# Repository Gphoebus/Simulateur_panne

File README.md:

<div align="center">

# 🔧 Simulateur de pannes BLE

**Carte d'interposition 4 voies pilotée par smartphone pour provoquer des pannes réalistes sur un système automatisé didactique, sans toucher au câblage.**

[Principe](#-principe) •
[Démarrage rapide](#-démarrage-rapide) •
[Matériel](#-matériel) •
[Firmware](#-firmware-esp32-c3) •
[Application](#-application-android-simu-pannes) •
[Protocole BLE](#-protocole-ble) •
[Sécurité](#%EF%B8%8F-sécurité--limites-dutilisation)

</div>

---

## 🎯 Pourquoi ce projet ?

En TP de maintenance, l'enseignant doit souvent débrancher un fil ou forcer une entrée **devant les élèves** pour créer une panne. Ce simulateur se place **une fois pour toutes** sur les liaisons *capteur → automate* ou *automate → actionneur*. Ensuite, depuis une tablette ou un téléphone, l'enseignant déclenche à distance :

- ✂️ un **fil coupé** (capteur débranché, actionneur non commandé),
- ⚡ un **forçage / court-circuit** (entrée bloquée à 0 ou à 1, dérive via résistance),
- 🎲 une panne **intermittente** (faux contact aléatoire).

Les élèves diagnostiquent avec leurs outils habituels (multimètre, mode visualisation de l'automate…). Un cavalier permet d'**éteindre les LEDs** de la carte pour que les pannes restent invisibles.

## ✨ Fonctionnalités

| | |
|---|---|
| 🔌 **4 voies d'interposition** | 2 relais de signal par voie, borniers à vis 3 points (IN / OUT / FLT) |
| 📱 **Pilotage BLE multi-boîtiers** | Une seule application gère tous les simulateurs de l'atelier en même temps |
| 🛡️ **Sécurité intrinsèque** | Relais au repos = liaison normale. Si l'ESP32 plante ou perd l'alimentation, le système fonctionne normalement |
| 🏷️ **Configuration dans le boîtier** | Nom, emplacement, identifiants (`%I0.2`, `%Q0.4`) et libellés des voies stockés en flash : un 2ᵉ téléphone retrouve la même configuration |
| 🔐 **Code PIN** | Empêche une autre application BLE (celle d'un élève…) de déclencher des pannes |
| 🔴 **Bouton RAZ** | Appui court : toutes les voies à l'état normal. Appui 8 s : PIN remis à `0000` |
| 🧪 **Mode démo** | L'interface s'ouvre dans Chrome sur PC avec 3 simulateurs fictifs, sans matériel |
| 💶 **Faible coût** | ≈ 28 € TTC port compris pour une carte (relevé du 15/11/2026) |

---

## 🧭 Principe

### Architecture du système

```mermaid
flowchart LR
    APP["📱 Appli Android<br/>Simu Pannes"] -- "BLE 5 (GATT)" --> ESP
    subgraph CARTE["Carte simulateur (PCB KiCad)"]
        ALIM["A — Alim 5 V / 2 A<br/>protection inversion + PTC + TVS"] --> ESP
        ESP["B — ESP32-C3 SuperMini"] --> ULN["C — ULN2803A<br/>+ LEDs d'état"]
        ULN --> V["D — 4 voies<br/>8 relais signal"]
    end
    CAP["Capteur / sortie automate"] -- IN --> V
    V -- OUT --> PLC["Entrée automate / actionneur"]
    REF["Référence de panne<br/>0 V, +24 V, résistance"] -- FLT --> V
```

### Une voie d'interposition = 2 relais

```
              K_A (repos)                    Bornier J4..J7
 IN  o────────NC ┐                           1 : IN  = côté source
                 COM ───────────── o OUT      (capteur ou sortie automate)
           ┌──NO ┘                           2 : OUT = côté destination
           │ (nœud X)                         (entrée automate ou actionneur)
           └── COM K_B ── NC : en l'air      3 : FLT = référence de panne
                       └─ NO ──────── o FLT   (0 V, +24 V, résistance…)
```

| Mode | Relais A | Relais B | Effet sur OUT |
|---|:-:|:-:|---|
| **0 — Normal** | 0 | 0 | OUT = IN |
| **1 — Coupure** | 1 | 0 | OUT en l'air (fil coupé) |
| **2 — Forçage** | 1 | 1 | OUT = FLT |
| **3 — Coupure ~** | aléatoire | 0 | faux contact (0,1 s → période réglée) |
| **4 — Forçage ~** | aléatoire | 1 | forçage intermittent |

> [!NOTE]
> Ordre de commutation garanti par le firmware : **B se ferme avant A** et **A s'ouvre avant B**, pour qu'OUT ne passe jamais par un état « en l'air » parasite. Au démarrage, toutes les voies sont à l'état normal : les pannes ne sont **pas** mémorisées après une coupure d'alimentation.

---

## 🚀 Démarrage rapide

1. **Fabriquer la carte** : envoyer `Hardware_KiCad/production/Simulateur_panne.zip` (Gerber) chez un fabricant de PCB, puis souder les composants (tous traversants sauf Q1 en SOT-23).
2. **Flasher l'ESP32-C3** sans installer d'outil : ouvrir [esptool-js](https://espressif.github.io/esptool-js/) dans Chrome ou Edge, puis flasher `Logiciel/Firmware/bin/SimPanne_ESP32C3_v1.0.0_merged.bin` à l'adresse **`0x0`**.
3. **Installer l'application** : copier `Logiciel/SimuPannes.apk` sur la tablette, l'ouvrir et autoriser l'installation.
4. **Mettre en service** : alimenter le boîtier (LED à 2 Hz), appuyer sur **＋** dans l'appli, choisir `SP-NEW-xxxx`, PIN `0000`, puis configurer nom et voies.
5. **Câbler une voie** : IN = côté source, OUT = côté destination, FLT = référence de panne voulue.

> [!TIP]
> Pour présenter l'outil sans matériel, ouvrez simplement [`Logiciel/Android/app/src/main/assets/index.html`](Logiciel/Android/app/src/main/assets/index.html) dans Chrome : le mode démo simule 3 boîtiers.

---

## 📁 Organisation du dépôt

```
Simulateur_panne/
├── Hardware_KiCad/                     ← carte électronique (KiCad 7 / 8 / 9)
│   ├── Simulateur_panne.kicad_pro      projet à ouvrir
│   ├── Simulateur_panne.kicad_sch      schéma A3
│   ├── Simulateur_panne.kicad_pcb      circuit imprimé routé
│   ├── Simulateur_panne.kicad_sym      symbole ESP32-C3 SuperMini
│   ├── Simulateur_panne.pretty/        empreinte ESP32-C3 SuperMini (sur support)
│   ├── exports/                        schéma PDF/PNG + nomenclature CSV
│   ├── production/                     Gerber, BOM et positions JLCPCB
│   └── README.md                       documentation matérielle détaillée
├── Logiciel/
│   ├── SimuPannes.apk                  application Android prête à installer
│   ├── Firmware/
│   │   ├── SimPanne_ESP32C3/           sketch Arduino (.ino + SimCore.h/.cpp)
│   │   ├── bin/                        firmware compilé (merged, adresse 0x0)
│   │   └── tests/test_core.cpp         tests unitaires du cœur (sur PC)
│   ├── Android/                        sources de l'appli (HTML/JS + Java)
│   └── README.md                       documentation logicielle détaillée
├── Nomenclature chiffrée — Simulateur de pannes.xlsx
└── qr.png                              QR code vers ce dépôt (sérigraphié sur le PCB)
```

---

## 🔩 Matériel

<p align="center">
  
  <br><em>Schéma complet (cliquer pour la version PDF)</em>
</p>

| Bloc | Rôle | Composants clés |
|---|---|---|
| **A — Alimentation** | 5 V / 2 A par jack 5,5×2,1 ou bornier | Q1 AO3401A (anti-inversion, chute < 0,1 V), F1 PTC 1,1 A, D1 TVS P6KE6.8A |
| **B — Microcontrôleur** | BLE 5, USB-C, 3,3 V intégré | ESP32-C3 SuperMini **sur support** (remplaçable), D2 1N5819, SW1 RAZ, J3 extension (I2C/UART) |
| **C — Commande relais** | 8 darlingtons avec roue libre intégrée | ULN2803A, 8 LEDs (orange = coupure, rouge = forçage), JP1 = LEDs ON/OFF |
| **D — 4 voies** | Interposition sur les liaisons | 8 relais signal 5 V, 4 borniers 3 points |

### Affectation des GPIO

| GPIO | 0 | 1 | 3 | 4 | 5 | 6 | 7 | 10 | 8 | 9 |
|---|---|---|---|---|---|---|---|---|---|---|
| **Rôle** | K1 V1-A | K2 V1-B | K3 V2-A | K4 V2-B | K5 V3-A | K6 V3-B | K7 V4-A | K8 V4-B | LED module | Bouton RAZ |

> [!IMPORTANT]
> GPIO2, GPIO8 et GPIO9 sont des **broches de strapping** : elles ne pilotent volontairement aucun relais, sinon le ULN2803A bloquerait le démarrage de l'ESP32.

### Consommation (sous 5 V)

| Poste | Courant |
|---|---|
| 8 bobines de relais (cas extrême) | 240 mA |
| 9 LEDs | 25 mA |
| ESP32-C3 en émission BLE (pic) | ≈ 350 mA |
| Extension J3 (réserve) | 200 mA |
| **Total maxi** | **≈ 0,8 A** → bloc secteur 2 A largement dimensionné |

Détails complets (justification des choix, exemples de raccordement, points de vigilance) : **[Hardware_KiCad/README.md](Hardware_KiCad/README.md)**.

---

## 💾 Firmware ESP32-C3

### Option 1 — Binaire précompilé (recommandé)
Flasher `Logiciel/Firmware/bin/SimPanne_ESP32C3_v1.0.0_merged.bin` à l'adresse **`0x0`** avec [esptool-js](https://espressif.github.io/esptool-js/) (Chrome / Edge + câble USB-C).

### Option 2 — Compilation avec Arduino IDE 2

| Élément | Version testée |
|---|---|
| Carte : *esp32 by Espressif* | 3.3.12 |
| Bibliothèque : *NimBLE-Arduino* (h2zero) | 2.5.2 |
| Type de carte | `ESP32C3 Dev Module` |
| Option | `USB CDC On Boot : Enabled` |

Ouvrir `SimPanne_ESP32C3.ino` puis téléverser. En cas d'échec : maintenir **BOOT**, appuyer sur **RESET**, relâcher BOOT.

### Signification de la LED du module

| Clignotement | État |
|---|---|
| Rapide (10 Hz) | Identification demandée depuis l'appli |
| 2 Hz | Boîtier **non configuré** |
| Éclair toutes les 3 s | Configuré, aucun téléphone connecté |
| Éclair toutes les secondes | Au moins un téléphone connecté |

### Tests unitaires
Le cœur (`SimCore`) est indépendant d'Arduino et testé sur PC : **58 vérifications** (PIN, configuration, ordre de commutation, intermittence, RAZ, retour usine, accents UTF-8).

```bash
cd Logiciel/Firmware
g++ -std=c++17 -I SimPanne_ESP32C3 tests/test_core.cpp SimPanne_ESP32C3/SimCore.cpp -o test_core && ./test_core
```

### Console série (115 200 bauds, optionnelle)
`HELP` · `SHOW` · `SET <voie> <mode>` · `ALL 0` · `PIN <code>` · `IDENT` · `RESETCFG` · `REBOOT` · `CFG …`

---

## 📱 Application Android « Simu Pannes »

| | |
|---|---|
| **Compatibilité** | Android 6 minimum, conçue pour Android 14 |
| **Installation** | `Logiciel/SimuPannes.apk` (hors Play Store : accepter l'avertissement Play Protect) |
| **Autorisations** | *Appareils à proximité* (Android 12+) ou *Localisation* activée (Android 6 à 11) |
| **Technologie** | Interface HTML/JS dans une WebView + couche BLE native en Java |

**En séance :**
- tableau de bord de tous les boîtiers, voies **ENTRÉE** (bleu) / **SORTIE** (orange), cadre rouge dès qu'une panne est active ;
- 5 touches par voie : **Normal · Coupure · Forçage · Coupure ~ · Forçage ~** ;
- la touche ne s'allume **qu'après confirmation du boîtier** (notification BLE) ;
- gros bouton **TOUT NORMAL — ATELIER** pour annuler toutes les pannes ;
- au relancement, l'appli relit configuration et état de chaque boîtier.

**Reconstruire l'APK** (Ubuntu ou WSL, sans Android Studio) :

```bash
sudo apt install android-sdk-platform-23 android-sdk-build-tools apksigner zipalign default-jdk
cd Logiciel/Android && ./build_apk.sh
```

---

## 📡 Protocole BLE

Idéal comme support de projet **NSI** : un élève peut écrire son propre client (Web Bluetooth, Python `bleak`, App Inventor…).

**Service :** `5f6d0001-1d9c-4c7e-a7b1-53494d50414e` — messages texte UTF-8, champs séparés par `|`.

| Caractéristique | UUID | Accès | Contenu |
|---|---|---|---|
| CONFIG | `5f6d0002-…` | lecture | `CFG\|fw\|mac\|configuré\|nom\|lieu\|période_ms\|T1\|ID1\|LB1\|…` |
| | | écriture (PIN) | `nom\|lieu\|période_ms\|T1\|ID1\|LB1\|…\|T4\|ID4\|LB4` (T = `E`, `S` ou `-`) |
| ETAT | `5f6d0003-…` | lecture, notification | `ST\|m1\|m2\|m3\|m4\|uptime_s\|nb_connexions\|configuré` |
| CMD | `5f6d0004-…` | écriture | `AUTH <pin>`, `SET <voie> <mode>`, `ALL 0`, `PIN <code>`, `IDENT`, `PING`, `RESETCFG`, `REBOOT` |
| REPONSE | `5f6d0005-…` | lecture, notification | `OK …` ou `ERR AUTH`, `ERR VOIE`, `ERR MODE`… |

- L'authentification `AUTH <pin>` est valable **pour une connexion** ; sans elle, seuls `PING`, `IDENT` et les lectures sont permis.
- **3 téléphones** maximum connectés simultanément au même boîtier.
- Longueurs max : nom 20, lieu 24, identifiant 12, libellé 24 octets.

<details>
<summary><b>Exemple de séquence</b></summary>

```text
→ CMD     : AUTH 0000
← REPONSE : OK AUTH
→ CMD     : SET 2 1          (voie 2 en coupure)
← REPONSE : OK SET 2 1
← ETAT    : ST|0|1|0|0|512|1|1
→ CMD     : ALL 0
← REPONSE : OK ALL 0
← ETAT    : ST|0|0|0|0|530|1|1
```
</details>

---

## 🔌 Exemples de raccordement

| Liaison | Câblage | Pannes obtenues |
|---|---|---|
| **Détecteur PNP 24 V** | IN = sortie capteur, OUT = entrée automate | FLT au 0 V → bloqué à 0 · FLT au +24 V → bloqué à 1 |
| **Boucle 4-20 mA** | Interposer sur un fil de la boucle | Coupure → 0 mA (rupture) · FLT via 250 Ω → dérive de mesure |
| **Commande d'actionneur 24 V** | IN = sortie automate, OUT = bobine contacteur / distributeur | Coupure → l'actionneur ne répond plus |

---

## ⚠️ Sécurité – limites d'utilisation

> [!CAUTION]
> - **TBTS uniquement : ≤ 30 V DC et ≤ 1 A par contact.**
> - **Jamais de 230 V AC** sur les borniers de voie.
> - **Ne jamais** s'interposer sur une chaîne de sécurité (arrêt d'urgence, carter, barrière immatérielle).
> - Pour un actionneur > 1 A, interposer sur la **commande** (bobine du contacteur), pas sur la puissance.

---

## 💶 Nomenclature et coût

Nomenclature chiffrée détaillée (références Reichelt / AliExpress, liens, remarques) : **[Nomenclature chiffrée — Simulateur de pannes.xlsx](Nomenclature%20chiffrée%20—%20Simulateur%20de%20pannes.xlsx)**.

| Poste | Montant TTC |
|---|---:|
| Composants Reichelt | 8,48 € |
| Port Reichelt | 9,48 € |
| Composants AliExpress (relais, ESP32-C3) | 5,29 € |
| Port AliExpress | 4,85 € |
| **Total pour 1 carte** | **≈ 28,10 €** (hors PCB et boîtier) |

*Prix relevés le 15/11/2026. Le coût unitaire baisse fortement pour une série (frais de port mutualisés, relais vendus par lot de 10).*

---

## 🎓 Usages pédagogiques

- **STI2D (ITEC / maintenance)** : démarche de diagnostic, lecture de schéma, mesures sur une chaîne d'information, analyse de la sécurité intrinsèque d'une conception.
- **NSI** : étude d'un protocole de communication (GATT, notifications), programmation d'un client BLE, tests unitaires d'un code embarqué, interface web.
- **Projet** : extension J3 disponible (écran OLED I2C, buzzer, UART) pour faire évoluer la carte.

---

## 🗺️ Feuille de route

- [x] Schéma et PCB KiCad v1.0
- [x] Firmware v1.0.0 (BLE NimBLE, PIN, 5 modes, configuration en flash)
- [x] Application Android v1.0.0 multi-boîtiers + mode démo
- [ ] Validation BLE sur le matériel réel
- [ ] Pannes **retardées** et **scénarios** enchaînés
- [ ] Boîtier imprimable en 3D
- [ ] Client Web Bluetooth (PC / Chromebook)

## 🤝 Contribuer

Les retours d'enseignants sont les bienvenus : ouvrez une [issue](https://github.com/Gphoebus/Simulateur_panne/issues) pour signaler un problème ou proposer un scénario de panne, ou une *pull request* pour une amélioration.

## 📄 Licence

À définir — voir [LICENSE](LICENSE).

---

<div align="center">

**Phoebus du F.L.A.L.** — Lycée de la Borde Basse — STI2D / NSI

</div>

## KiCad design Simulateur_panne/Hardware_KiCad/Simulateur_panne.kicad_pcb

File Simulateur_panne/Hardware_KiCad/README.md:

# Simulateur de pannes BLE – ESP32-C3 / 4 voies

Carte d'**interposition** qui se place sur une liaison **capteur → automate** ou
**automate → actionneur** d'un système automatisé didactique. Depuis une application
smartphone (BLE), l'enseignant provoque des pannes réalistes (fil coupé, court-circuit,
forçage, dérive) sans toucher au câblage pendant la séance.

*Phoebus du F.L.A.L. – Lycée de la Borde Basse – STI2D / NSI – Rév. 1.0 (13/11/2026)*

---

## 1. Contenu du dossier

| Fichier | Rôle |
|---|---|
| `Simulateur_panne.kicad_pro` | Projet KiCad (ouvrir celui-ci) |
| `Simulateur_panne.kicad_sch` | Schéma complet A3 (format KiCad 7, s'ouvre en KiCad 7 / 8 / 9) |
| `Simulateur_panne.kicad_sym` | Bibliothèque projet : symbole `ESP32-C3_SuperMini` |
| `Simulateur_panne.pretty/` | Bibliothèque projet : empreinte `ESP32-C3_SuperMini_Socket` |
| `sym-lib-table`, `fp-lib-table` | Déclarent ces bibliothèques locales (`${KIPRJMOD}`) |
| `exports/Schema_Simulateur_panne.pdf` / `.png` | Schéma imprimable |
| `exports/BOM_Simulateur_panne.csv` | Nomenclature (séparateur `;`, s'ouvre dans Excel) |

## 2. Principe d'une voie d'interposition

Chaque voie dispose d'un bornier 3 points et de **2 relais** :

```
              K_A (repos)                    Bornier J4..J7
 IN  o────────NC ┐                           1 : IN  = côté source
                 COM ───────────── o OUT      (capteur ou sortie automate)
           ┌──NO ┘                           2 : OUT = côté destination
           │ (nœud X)                         (entrée automate ou actionneur)
           └── COM K_B ── NC : en l'air      3 : FLT = référence de panne
                       └─ NO ──────── o FLT   (0 V, +24 V, résistance…)
```

| K_A | K_B | État de la liaison | Panne simulée |
|:-:|:-:|---|---|
| 0 | x | OUT = IN | **Fonctionnement normal** |
| 1 | 0 | OUT en l'air | **Fil coupé**, capteur débranché, actionneur non commandé |
| 1 | 1 | OUT = FLT | **Forçage / court-circuit** (FLT câblé au 0 V, au +24 V ou via une résistance pour une dérive) |

Pannes « logicielles » gérées par le firmware : **intermittente** (K_A clignote),
**retardée** (déclenchement après N s), **scénarios** enchaînés.

> **Sécurité intrinsèque** : relais au repos = liaison normale. Si l'ESP32 plante,
> redémarre ou perd l'alimentation, le système automatisé fonctionne normalement.

## 3. Architecture (blocs du schéma)

**A – Alimentation 5 V / 2 A**
- Entrée par jack 5,5 × 2,1 (J1) **ou** bornier (J2).
- **Q1 AO3401A** (P-MOS) : protection contre l'inversion de polarité avec une chute
  < 0,1 V. Une diode série ferait perdre 0,4 V : les bobines n'auraient plus que
  ≈ 3,7 V après le ULN2803A, sous le seuil d'enclenchement du relais (3,75 V).
- **F1** PTC réarmable 1,1 A, **D1** TVS P6KE6.8A (surtensions), C1 470 µF + C2 100 nF.
- LED verte D3 « sous tension ».

**B – Module ESP32-C3 SuperMini** (BLE 5, USB-C, régulateur 3,3 V intégré)
- Monté sur 2 barrettes femelles 1×08 (entraxe 15,24 mm) : remplaçable, programmable par USB-C.
- **D2 1N5819** : empêche le 5 V de l'USB de remonter vers la carte (et inversement).
- **SW1** sur GPIO9 : bouton « RAZ des pannes » en façade (pull-up déjà présente sur le module).
- **J3** extension : 3V3, GND, GPIO2, GPIO20 (RX), GPIO21 (TX), +5V → écran OLED I2C, buzzer, debug.

**C – Commande des relais**
- **ULN2803A** : 8 darlingtons, diodes de roue libre intégrées (COM au +5 V). Entrées
  compatibles 3,3 V, résistance de rappel interne → relais au repos pendant le boot.
- 8 LEDs (orange = K_A « coupure », rouge = K_B « forçage »).
- **JP1** : cavalier retiré = LEDs éteintes → pannes invisibles pour les élèves.

**D – 4 voies** : K1…K8 = **Omron G5V-1** (relais de signal, contacts adaptés aux
faibles courants : entrées automate, boucles 4-20 mA, capteurs).

## 4. Affectation des GPIO

| GPIO | Fonction | | GPIO | Fonction |
|---|---|---|---|---|
| 0 | K1 – voie 1 A | | 5 | K5 – voie 3 A |
| 1 | K2 – voie 1 B | | 6 | K6 – voie 3 B |
| 3 | K3 – voie 2 A | | 7 | K7 – voie 4 A |
| 4 | K4 – voie 2 B | | 10 | K8 – voie 4 B |
| 9 | Bouton RAZ (SW1) | | 2 / 20 / 21 | Extension J3 |
| 8 | LED du module (non utilisé) | | 18 / 19 | USB (non accessible) |

GPIO2, GPIO8 et GPIO9 sont des **broches de strapping** : elles ne pilotent pas de
relais, sinon le ULN2803A (qui tire vers 0 V) bloquerait le démarrage.

## 5. Bilan de consommation (sous 5 V)

| Poste | Courant |
|---|---|
| 8 bobines G5V-1 (30 mA) – cas extrême | 240 mA |
| 9 LEDs (≈ 2,5 mA) | 25 mA |
| ESP32-C3 en émission BLE (pic) | ≈ 350 mA |
| Extension J3 (réserve) | 200 mA |
| **Total maxi** | **≈ 0,8 A** → alimentation 2 A largement dimensionnée |

## 6. Exemples de raccordement

- **Détecteur PNP 24 V** : IN = fil noir (sortie) du capteur, OUT = entrée automate.
  FLT au 0 V → « capteur bloqué à 0 » ; FLT au +24 V → « capteur bloqué à 1 ».
- **Boucle 4-20 mA** : interposer sur un fil de la boucle. Coupure → 0 mA (rupture
  détectée par l'automate) ; FLT relié à l'autre fil via 250 Ω → dérive de mesure.
- **Commande d'actionneur 24 V** (bobine de contacteur, distributeur) : IN = sortie
  automate, OUT = actionneur. Coupure → l'actionneur ne répond plus à l'ordre.

## 7. Limites et sécurité – à respecter impérativement

- **TBTS uniquement : ≤ 30 V DC, ≤ 1 A par contact** (G5V-1 : 1 A / 24 V DC).
- **Jamais de 230 V AC** sur les borniers de voie.
- Ne **jamais** s'interposer sur une chaîne de sécurité (arrêt d'urgence, carter,
  barrière immatérielle).
- Pour des actionneurs > 1 A, interposer sur la **commande** (bobine du
  contacteur / relais d'interface), pas sur la puissance.

## 8. Points à vérifier avant le routage du PCB

1. **Brochage du SuperMini** : il existe plusieurs variantes de clones. Vérifier la
   correspondance broches/GPIO de votre module avec l'empreinte (broche 1 = 5 V,
   côté USB-C) avant de lancer la fabrication.
2. **F1** : l'empreinte `Fuse_Bourns_MF-RHT100` (pas 5,1 mm) est compatible MF-R110 ;
   à vérifier selon la référence achetée.
3. Q1 (SOT-23) est le seul composant CMS : se soude facilement au fer.
4. Dans KiCad 8/9 : lancer *Inspecter → Contrôle des règles électriques (ERC)*.
   Les seules broches non connectées (marquées ✕) sont volontaires : NC des relais B
   et GPIO8.

## 9. Étapes suivantes proposées

1. Routage du PCB (format 100 × 80 mm, borniers sur un seul bord).
2. Firmware ESP32-C3 (Arduino / PlatformIO) : service BLE GATT
   *Simulateur_panne* avec une caractéristique d'écriture par voie
   (`0 = normal`, `1 = coupure`, `2 = forçage`, `3 = intermittent`) et une
   caractéristique de notification de l'état.
3. Application smartphone (MIT App Inventor ou appli web Web Bluetooth).

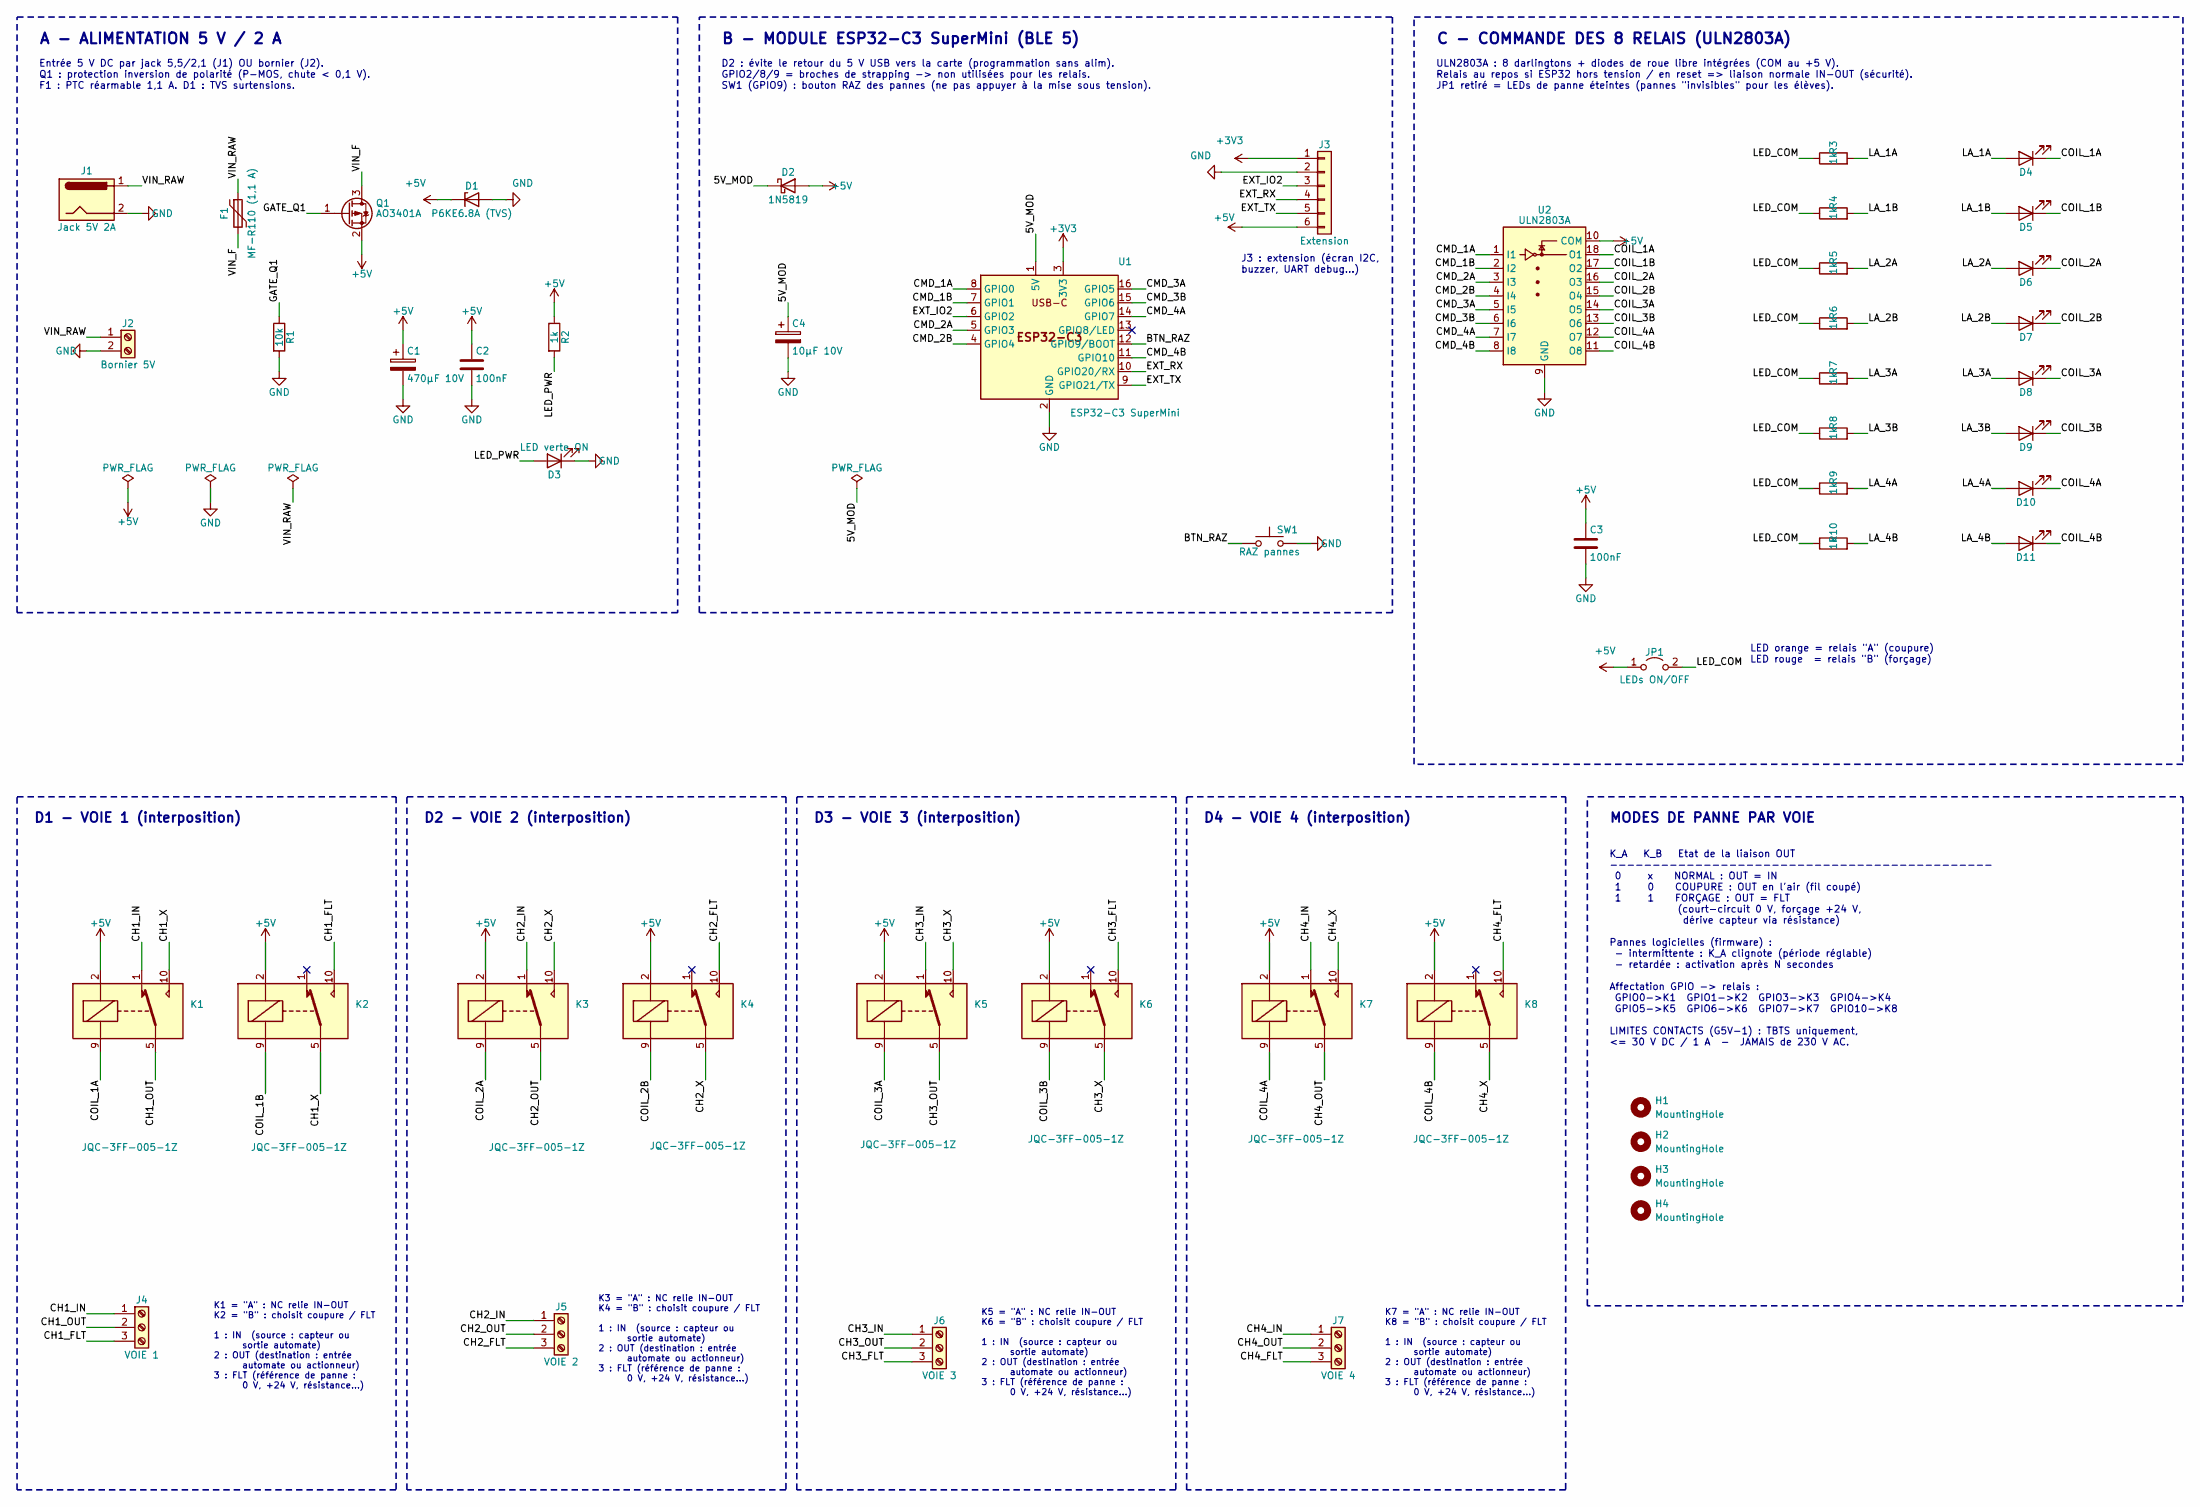
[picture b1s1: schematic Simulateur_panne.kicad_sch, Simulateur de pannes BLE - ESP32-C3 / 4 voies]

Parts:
C1: 470µF 10V; CP_Radial_D8.0mm_P3.50mm
C2, C3: 100nF; C_Disc_D5.0mm_W2.5mm_P5.00mm
C4: 10µF 10V; CP_Radial_D5.0mm_P2.00mm
D1: P6KE6.8A (TVS); D_DO-15_P10.16mm_Horizontal
D2: 1N5819; D_DO-41_SOD81_P10.16mm_Horizontal
D3: LED verte ON; LED_D3.0mm
D4, D6, D8, D10: LED orange; LED_D3.0mm
D5, D7, D9, D11: LED rouge; LED_D3.0mm
F1: MF-R110 (1,1 A); RV_Disc_D9mm_W3.6mm_P5mm
H1, H2, H3, H4: MountingHole; MountingHole_3.2mm_M3_ISO14580
J1: Jack 5V 2A; BarrelJack_Horizontal
J2: Bornier 5V; TerminalBlock_Phoenix_MKDS-1,5-2-5.08_1x02_P5.08mm_Horizont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
J3: Extension; PinHeader_1x06_P2.54mm_Vertical; JLCPCB C37208
J4: VOIE 1; TerminalBlock_Phoenix_MKDS-1,5-3-5.08_1x03_P5.08mm_Horizont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; JLCPCB C72334
J5: VOIE 2; TerminalBlock_Phoenix_MKDS-1,5-3-5.08_1x03_P5.08mm_Horizont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
J6: VOIE 3; TerminalBlock_Phoenix_MKDS-1,5-3-5.08_1x03_P5.08mm_Horizont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
J7: VOIE 4; TerminalBlock_Phoenix_MKDS-1,5-3-5.08_1x03_P5.08mm_Horizont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
JP1: LEDs ON/OFF; PinHeader_1x02_P2.54mm_Vertical
K1: JQC-3FF-005-1Z; Relay_SPDT_Omron_G5V-1; JLCPCB C28695
K2, K3, K4, K5, K6, K7, K8: JQC-3FF-005-1Z; Relay_SPDT_Omron_G5V-1
Q1: AO3401A; SOT-23
R1: 10k; R_Axial_DIN0207_L6.3mm_D2.5mm_P10.16mm_Horizontal
R2, R3, R4, R5, R6, R7, R8, R9, R10: 1k; R_Axial_DIN0207_L6.3mm_D2.5mm_P10.16mm_Horizontal
SW1: RAZ pannes; SW_PUSH_6mm
U1: ESP32-C3 SuperMini; ESP32-C3_SuperMini_Socket
U2: ULN2803A; DIP-18_W7.62mm_Socket; JLCPCB C73936

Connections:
+3V3: J3.1, U1.3 (3V3)
+5V: C1.1, C2.1, C3.1, D1.1 (K), D2.2 (A), J3.6, JP1.1 (A), K1.2, K2.2, K3.2, K4.2, K5.2, K6.2, K7.2, K8.2, Q1.2 (S), R2.1, U2.10 (COM)
/5V_MOD: C4.1, D2.1 (K), U1.1 (5V)
/BTN_RAZ: SW1.1, U1.12 (GPIO9/BOOT)
/CH1_FLT: J4.3, K2.10
/CH1_IN: J4.1, K1.1
/CH1_OUT: J4.2, K1.5, K1.6
/CH1_X: K1.10, K2.5, K2.6
/CH2_FLT: J5.3, K4.10
/CH2_IN: J5.1, K3.1
/CH2_OUT: J5.2, K3.5, K3.6
/CH2_X: K3.10, K4.5, K4.6
/CH3_FLT: J6.3, K6.10
/CH3_IN: J6.1, K5.1
/CH3_OUT: J6.2, K5.5, K5.6
/CH3_X: K5.10, K6.5, K6.6
/CH4_FLT: J7.3, K8.10
/CH4_IN: J7.1, K7.1
/CH4_OUT: J7.2, K7.5, K7.6
/CH4_X: K7.10, K8.5, K8.6
/CMD_1A: U1.8 (GPIO0), U2.1 (I1)
/CMD_1B: U1.7 (GPIO1), U2.2 (I2)
/CMD_2A: U1.5 (GPIO3), U2.3 (I3)
/CMD_2B: U1.4 (GPIO4), U2.4 (I4)
/CMD_3A: U1.16 (GPIO5), U2.5 (I5)
/CMD_3B: U1.15 (GPIO6), U2.6 (I6)
/CMD_4A: U1.14 (GPIO7), U2.7 (I7)
/CMD_4B: U1.11 (GPIO10), U2.8 (I8)
/COIL_1A: D4.1 (K), K1.9, U2.18 (O1)
/COIL_1B: D5.1 (K), K2.9, U2.17 (O2)
/COIL_2A: D6.1 (K), K3.9, U2.16 (O3)
/COIL_2B: D7.1 (K), K4.9, U2.15 (O4)
/COIL_3A: D8.1 (K), K5.9, U2.14 (O5)
/COIL_3B: D9.1 (K), K6.9, U2.13 (O6)
/COIL_4A: D10.1 (K), K7.9, U2.12 (O7)
/COIL_4B: D11.1 (K), K8.9, U2.11 (O8)
/EXT_IO2: J3.3, U1.6 (GPIO2)
/EXT_RX: J3.4, U1.10 (GPIO20/RX)
/EXT_TX: J3.5, U1.9 (GPIO21/TX)
/GATE_Q1: Q1.1 (G), R1.1
/LA_1A: D4.2 (A), R3.2
/LA_1B: D5.2 (A), R4.2
/LA_2A: D6.2 (A), R5.2
/LA_2B: D7.2 (A), R6.2
/LA_3A: D8.2 (A), R7.2
/LA_3B: D9.2 (A), R8.2
/LA_4A: D10.2 (A), R9.2
/LA_4B: D11.2 (A), R10.2
/LED_COM: JP1.2 (B), R3.1, R4.1, R5.1, R6.1, R7.1, R8.1, R9.1, R10.1
/LED_PWR: D3.2 (A), R2.2
/VIN_F: F1.2, Q1.3 (D)
/VIN_RAW: F1.1, J1.1, J2.1
GND: C1.2, C2.2, C3.2, C4.2, D1.2 (A), D3.1 (K), J1.2, J2.2, J3.2, R1.2, SW1.2, U1.2 (GND), U2.9 (GND)

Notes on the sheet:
D2 : évite le retour du 5 V USB vers la carte (programmation sans alim). GPIO2/8/9 = broches de strapping -> non utilisées pour les relais. SW1 (GPIO9) : bouton RAZ des pannes (ne pas appuyer à la mise sous tension).
K7 = "A" : NC relie IN-OUT K8 = "B" : choisit coupure / FLT 1 : IN (source : capteur ou sortie automate) 2 : OUT (destination : entrée automate ou actionneur) 3 : FLT (référence de panne : 0 V, +24 V, résistance...)
K5 = "A" : NC relie IN-OUT K6 = "B" : choisit coupure / FLT 1 : IN (source : capteur ou sortie automate) 2 : OUT (destination : entrée automate ou actionneur) 3 : FLT (référence de panne : 0 V, +24 V, résistance...)
C - COMMANDE DES 8 RELAIS (ULN2803A)
ULN2803A : 8 darlingtons + diodes de roue libre intégrées (COM au +5 V). Relais au repos si ESP32 hors tension / en reset => liaison normale IN-OUT (sécurité). JP1 retiré = LEDs de panne éteintes (pannes "invisibles" pour les élèves).
D1 - VOIE 1 (interposition)
B - MODULE ESP32-C3 SuperMini (BLE 5)
K1 = "A" : NC relie IN-OUT K2 = "B" : choisit coupure / FLT 1 : IN (source : capteur ou sortie automate) 2 : OUT (destination : entrée automate ou actionneur) 3 : FLT (référence de panne : 0 V, +24 V, résistance...)
J3 : extension (écran I2C, buzzer, UART debug...)
K_A K_B Etat de la liaison OUT --------------------------------------------- 0 x NORMAL : OUT = IN 1 0 COUPURE : OUT en l'air (fil coupé) 1 1 FORÇAGE : OUT = FLT (court-circuit 0 V, forçage +24 V, dérive capteur via résistance) Pannes logicielles (firmware) : - intermittente : K_A clignote (période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
A - ALIMENTATION 5 V / 2 A
LED orange = relais "A" (coupure) LED rouge = relais "B" (forçage)
D3 - VOIE 3 (interposition)
MODES DE PANNE PAR VOIE
K3 = "A" : NC relie IN-OUT K4 = "B" : choisit coupure / FLT 1 : IN (source : capteur ou sortie automate) 2 : OUT (destination : entrée automate ou actionneur) 3 : FLT (référence de panne : 0 V, +24 V, résistance...)
D4 - VOIE 4 (interposition)
D2 - VOIE 2 (interposition)
Entrée 5 V DC par jack 5,5/2,1 (J1) OU bornier (J2). Q1 : protection inversion de polarité (P-MOS, chute < 0,1 V). F1 : PTC réarmable 1,1 A. D1 : TVS surtensions.

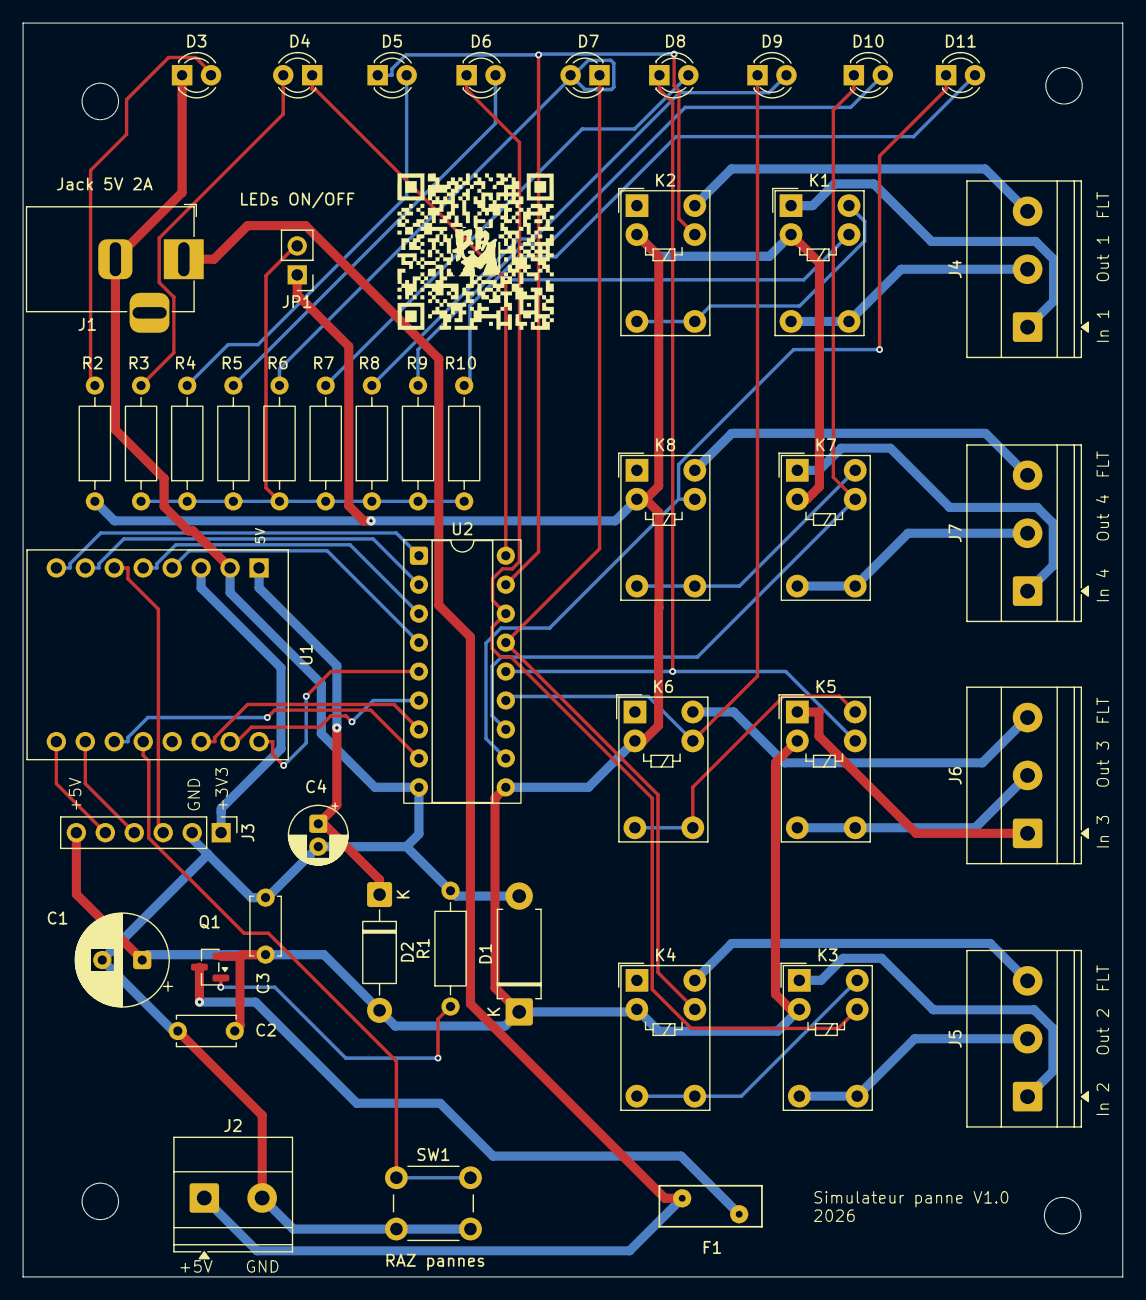
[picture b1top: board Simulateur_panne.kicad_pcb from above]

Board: 2 copper layers, 96.5 x 110.0 mm, 52 parts (1 on the bottom side), 53 nets.

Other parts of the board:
G1: LOGO; logo_phm
G2: LOGO; logo_qr_code_simulateur_panne

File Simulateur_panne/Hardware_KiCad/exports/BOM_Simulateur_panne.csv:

Repères;Qté;Valeur;Description;Empreinte
C1;1;470µF 10V;Condensateur électrolytique;Capacitor_THT:CP_Radial_D8.0mm_P3.50mm
C2,C3;2;100nF;Condensateur céramique 50 V;Capacitor_THT:C_Disc_D5.0mm_W2.5mm_P5.00mm
C4;1;10µF 10V;Condensateur électrolytique;Capacitor_THT:CP_Radial_D5.0mm_P2.00mm
D1;1;P6KE6.8A (TVS);Diode TVS unidirectionnelle 600 W;Diode_THT:D_DO-15_P10.16mm_Horizontal
D2;1;1N5819;Diode Schottky 1 A 40 V;Diode_THT:D_DO-41_SOD81_P10.16mm_Horizontal
D3;1;LED verte ON;LED 3 mm;LED_THT:LED_D3.0mm
D4,D6,D8,D10;4;LED orange;LED 3 mm;LED_THT:LED_D3.0mm
D5,D7,D9,D11;4;LED rouge;LED 3 mm;LED_THT:LED_D3.0mm
F1;1;MF-R110 (1,1 A);Fusible réarmable PTC radial;Fuse:Fuse_Bourns_MF-RHT100
J1;1;Jack 5V 2A;Embase jack DC 5,5 x 2,1 mm;Connector_BarrelJack:BarrelJack_Horizontal
J2;1;Bornier 5V;Bornier à vis 2 pts pas 5,08;TerminalBlock_Phoenix:TerminalBlock_Phoenix_MKDS-1,5-2-5.08_1x02_P5.08mm_Horizontal
J3;1;Extension;Barrette mâle 1x06 pas 2,54;Connector_PinHeader_2.54mm:PinHeader_1x06_P2.54mm_Vertical
J4;1;VOIE 1;Bornier à vis 3 pts pas 5,08;TerminalBlock_Phoenix:TerminalBlock_Phoenix_MKDS-1,5-3-5.08_1x03_P5.08mm_Horizontal
J5;1;VOIE 2;Bornier à vis 3 pts pas 5,08;TerminalBlock_Phoenix:TerminalBlock_Phoenix_MKDS-1,5-3-5.08_1x03_P5.08mm_Horizontal
J6;1;VOIE 3;Bornier à vis 3 pts pas 5,08;TerminalBlock_Phoenix:TerminalBlock_Phoenix_MKDS-1,5-3-5.08_1x03_P5.08mm_Horizontal
J7;1;VOIE 4;Bornier à vis 3 pts pas 5,08;TerminalBlock_Phoenix:TerminalBlock_Phoenix_MKDS-1,5-3-5.08_1x03_P5.08mm_Horizontal
JP1;1;LEDs ON/OFF;Barrette 1x02 + cavalier;Connector_PinHeader_2.54mm:PinHeader_1x02_P2.54mm_Vertical
K1,K2,K3,K4,K5,K6,K7,K8;8;G5V-1;Relais signal Omron G5V-1 5 V DC (SPDT, 1 A 24 V DC);Relay_THT:Relay_SPDT_Omron_G5V-1
Q1;1;AO3401A;MOSFET canal P 30 V 4 A (protection inversion);Package_TO_SOT_SMD:SOT-23
R1;1;10k;Résistance 1/4 W 5 %;Resistor_THT:R_Axial_DIN0207_L6.3mm_D2.5mm_P10.16mm_Horizontal
R2,R3,R4,R5,R6,R7,R8,R9,R10;9;1k;Résistance 1/4 W 5 %;Resistor_THT:R_Axial_DIN0207_L6.3mm_D2.5mm_P10.16mm_Horizontal
SW1;1;RAZ pannes;Bouton poussoir 6x6 mm;Button_Switch_THT:SW_PUSH_6mm
U1;1;ESP32-C3 SuperMini;Module ESP32-C3 SuperMini + 2 barrettes femelles 1x08;Simulateur_panne:ESP32-C3_SuperMini_Socket
U2;1;ULN2803A;Réseau 8 darlingtons (DIP-18 + support);Package_DIP:DIP-18_W7.62mm_Socket
